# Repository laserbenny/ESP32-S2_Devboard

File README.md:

# ESP32-S2_Devboard

This bare minimum board uses the ESP32-S2 module, it is designed to use minimal amount of current during sleep. All signals are routed to the edge of the PCB, it is also designed to fit in a breadboard.

The module is NOT 5V tolerant so make sure your UART is only 3.3V!  

1. To program the MCU first connect the UART to the RX, TX and GND pins.
2. Hold down RST and press BOOT, release the RST button and then the BOOT button.
3. The MCU shall now be in bootloader mode and can be programmed with Arduino

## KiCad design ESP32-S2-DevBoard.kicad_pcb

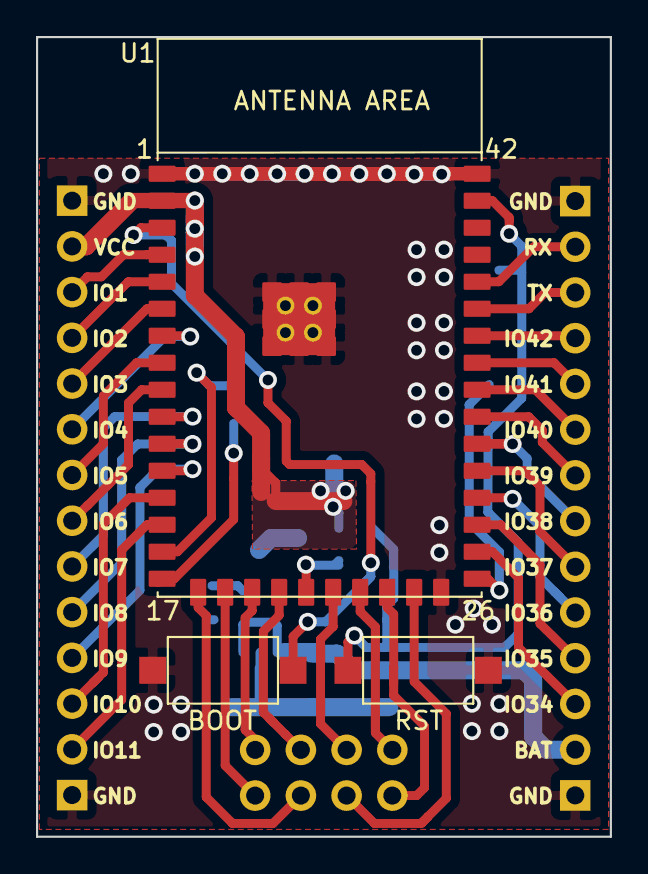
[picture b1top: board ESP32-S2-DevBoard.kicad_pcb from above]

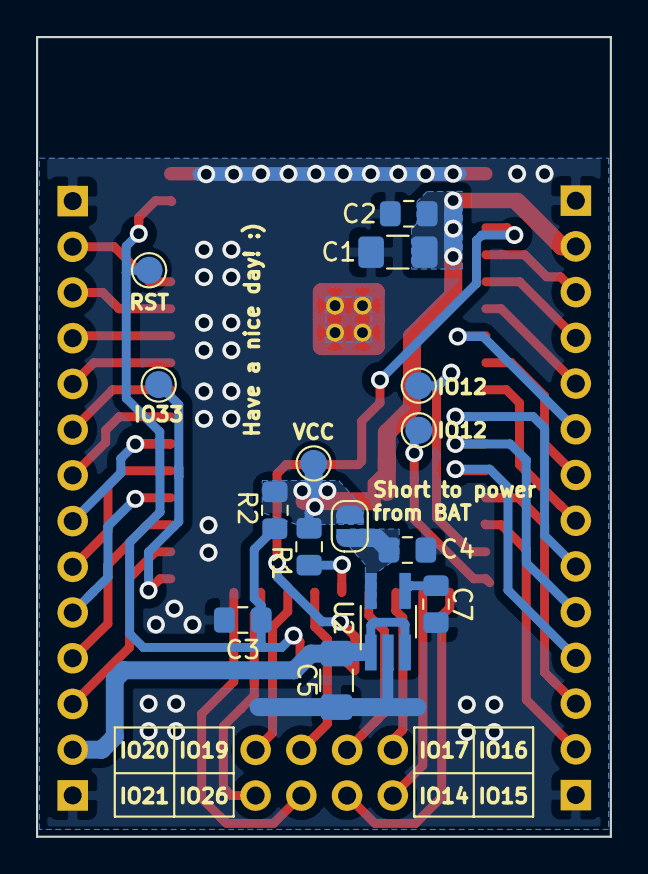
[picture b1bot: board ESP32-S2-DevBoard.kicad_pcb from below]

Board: 2 copper layers, 31.9 x 44.4 mm, 21 parts (15 on the bottom side), 41 nets.

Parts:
C1, C5: 47uF; C_1206_3216Metric_Pad1.42x1.75mm_HandSolder
C2, C3, C4, C7: 100n; C_0805_2012Metric_Pad1.15x1.40mm_HandSolder
J2, J6: Conn_01x14; PinSocket_1x14_P2.54mm_Vertical_2
J5: Conn_02x04_Counter_Clockwise; PinSocket_2x04_P2.54mm_Vertical2
JP1: SolderJumper_2_Open; SolderJumper-2_P1.3mm_Open_RoundedPad1.0x1.5mm
R1, R2: 10k; R_0805_2012Metric_Pad1.15x1.40mm_HandSolder
SW1: BOOT; SW_SPST_CK_RS282G05A3
SW2: RST; SW_SPST_CK_RS282G05A3
TP1: VCC; TestPoint_Pad_D1.5mm
TP2: RST; TestPoint_Pad_D1.5mm
TP3, TP5: IO12; TestPoint_Pad_D1.5mm
TP4: IO33; TestPoint_Pad_D1.5mm
U1: esp32-s2-wroom; esp32-s2-wrooom
U2: SP6205EM5; TSOT-23-5_HandSoldering

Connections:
+BATT: C5.2, J6.13, U2.1, U2.3
GND: C1.2, C2.2, C3.2, C4.1, C5.1, C7.1, J2.1, J2.14, J6.1, J6.14, SW1.1, SW2.2, U1.1, U1.26, U1.42, U1.43, U2.2
IO14: J5.5, U1.17
IO15: J5.7, U1.18
IO16: J5.8, U1.19
IO17: J5.6, U1.20
IO19: J5.4, U1.22
IO20: J5.2, U1.23
IO21: J5.1, U1.24
IO26: J5.3, U1.25
unnamed: C3.1, R2.2, SW2.1, TP2.1, U1.41
unnamed: C4.2, JP1.2, U2.5
unnamed: C7.2, U2.4
unnamed: J2.2, U1.14
unnamed: J2.3, U1.13
unnamed: J2.4, U1.12
unnamed: J2.5, U1.11
unnamed: J2.6, U1.10
unnamed: J2.7, U1.9
unnamed: J2.8, U1.8
unnamed: J2.9, U1.7
unnamed: J2.10, U1.6
unnamed: J2.11, U1.5
unnamed: J2.12, U1.4
unnamed: J6.2, U1.38
unnamed: J6.3, U1.37
unnamed: J6.4, U1.36
unnamed: J6.5, U1.35
unnamed: J6.6, U1.34
unnamed: J6.7, U1.33
unnamed: J6.8, U1.32
unnamed: J6.9, U1.31
unnamed: J6.10, U1.30
unnamed: J6.11, U1.29
unnamed: J6.12, U1.28
unnamed: R1.2, U1.21
unnamed: SW1.2, U1.3
unnamed: TP3.1, U1.15
unnamed: TP4.1, U1.27
unnamed: TP5.1, U1.16
VCC: C1.1, C2.1, J2.13, JP1.1, R1.1, R2.1, TP1.1, U1.2
